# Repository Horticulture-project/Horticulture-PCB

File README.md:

# Horticulture-PCB
Horticulture PCB's

## BOM:
https://htmlpreview.github.io/?https://github.com/Horticulture-project/Horticulture-PCB/blob/master/bom/ibom.html

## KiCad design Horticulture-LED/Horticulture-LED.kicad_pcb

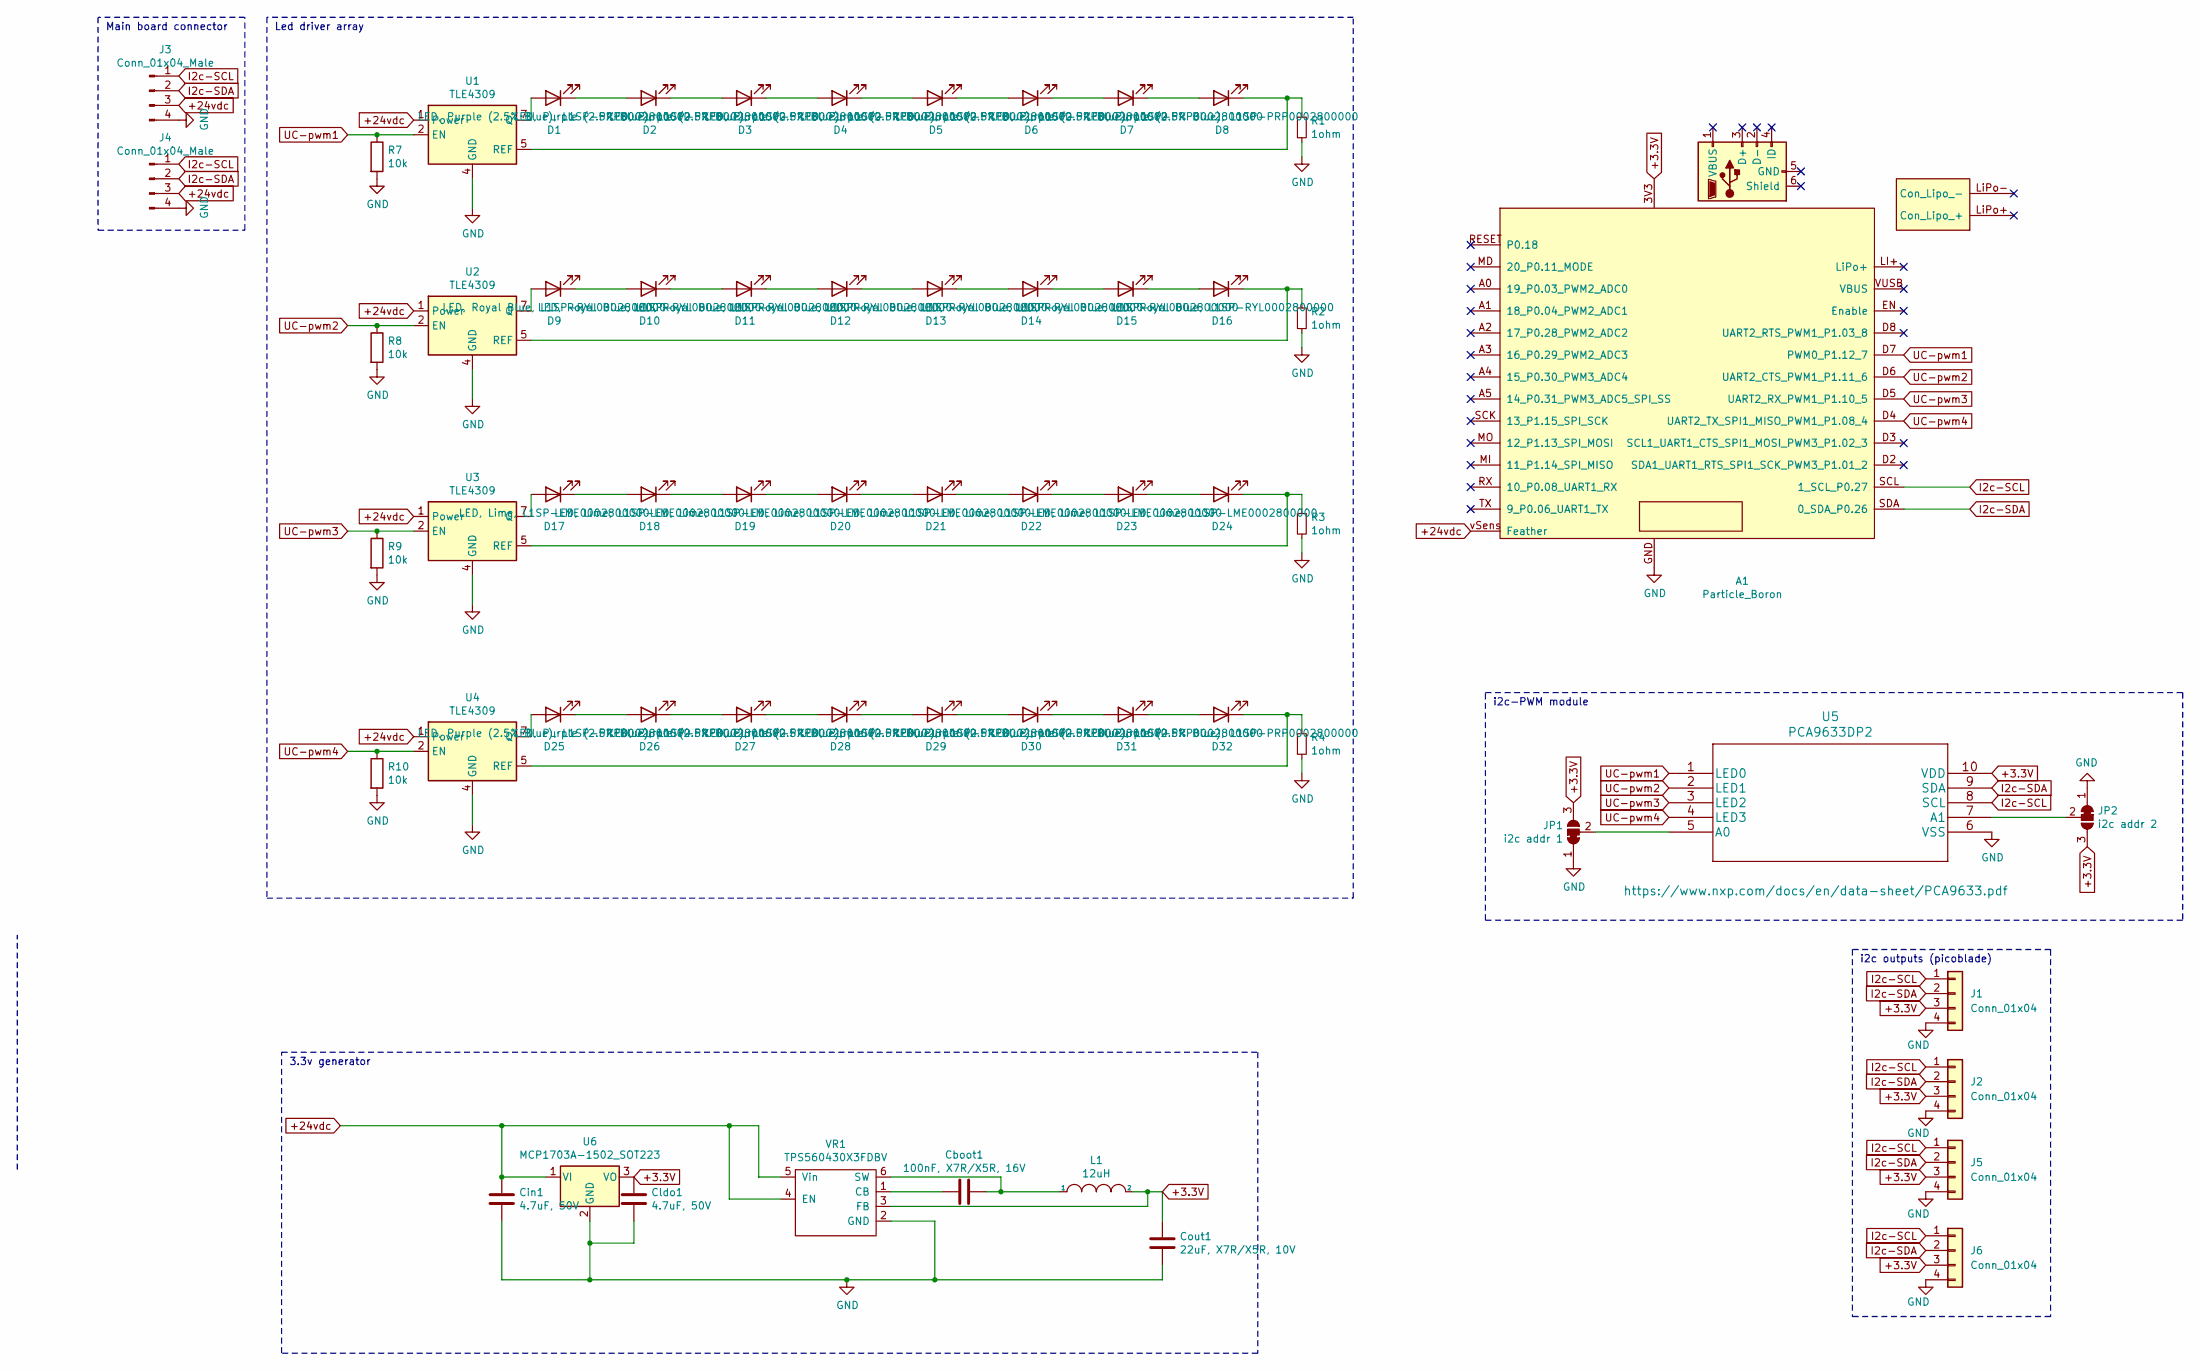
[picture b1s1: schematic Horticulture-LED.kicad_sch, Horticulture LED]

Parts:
A1: Particle_Boron; PCB_FeatherWing
Cboot1: 100nF, X7R/X5R, 16V; C_0805_2012Metric
Cin1: 4.7uF, 50V; C_1206_3216Metric
Cldo1: 4.7uF, 50V; C_1206_3216Metric
Cout1: 22uF, X7R/X5R, 10V; C_0805_2012Metric
D1, D2, D3, D4, D5, D6, D7, D8, D25, D26, D27, D28, D29, D30, D31, D32: LED, Purple (2.5% Blue), L1SP-PRP0002800000; Sunplus-2835
D9, D10, D11, D12, D13, D14, D15, D16: LED, Royal Blue, L1SP-RYL0002800000; Sunplus-2835
D17, D18, D19, D20, D21, D22, D23, D24: LED, Lime, L1SP-LME0002800000; Sunplus-2835
J1, J2, J5, J6: Conn_01x04; Molex_PicoBlade_53398-0471_1x04-1MP_P1.25mm_Vertical
J3, J4: Conn_01x04_Male; JST_XH_S4B-XH-A-1_1x04_P2.50mm_Horizontal-SMD
JP1: i2c addr 1; SolderJumper-3_P1.3mm_Bridged12_RoundedPad1.0x1.5mm_NumberL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
JP2: i2c addr 2; SolderJumper-3_P1.3mm_Bridged12_RoundedPad1.0x1.5mm_NumberL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
L1: 12uH; IND_SDR0403-120ML
R1, R2, R3, R4: 1ohm; R_0805_2012Metric
R7, R8, R9, R10: 10k; R_0402_1005Metric
U1, U2, U3, U4: TLE4309; TO-263-7_TabPin4
U5: PCA9633DP2; SOT-552-1-nxp
U6: MCP1703A-1502_SOT223; SOT-223-3_TabPin2
VR1: TPS560430X3FDBV; SOT-23-6

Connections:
+3.3V: A1.3V3, Cldo1.1, Cout1.1, J1.3, J2.3, J5.3, J6.3, JP1.3 (B), JP2.3 (B), L1.2, U5.10 (VDD), U6.3 (VO), VR1.3 (FB)
+24vdc: A1.vSens (Feather), Cin1.1, J3.3, J4.3, U1.1 (Power), U2.1 (Power), U3.1 (Power), U4.1 (Power), U6.1 (VI), VR1.4 (EN), VR1.5 (Vin)
GND: A1.GND, Cin1.2, Cldo1.2, Cout1.2, J1.4, J2.4, J3.4, J4.4, J5.4, J6.4, JP1.1 (A), JP2.1 (A), R1.2, R2.2, R3.2, R4.2, R7.2, R8.2, R9.2, R10.2, U1.4 (GND), U2.4 (GND), U3.4 (GND), U4.4 (GND), U5.6 (VSS), U6.2 (GND), VR1.2 (GND)
I2c-SCL: A1.SCL (1_SCL_P0.27), J1.1, J2.1, J3.1, J4.1, J5.1, J6.1, U5.8 (SCL)
I2c-SDA: A1.SDA (0_SDA_P0.26), J1.2, J2.2, J3.2, J4.2, J5.2, J6.2, U5.9 (SDA)
unnamed: Cboot1.1, L1.1, VR1.6 (SW)
unnamed: Cboot1.2, VR1.1 (CB)
unnamed: D1.1 (K), D2.2 (A)
unnamed: D1.2 (A), U1.7 (Q)
unnamed: D2.1 (K), D3.2 (A)
unnamed: D3.1 (K), D4.2 (A)
unnamed: D4.1 (K), D5.2 (A)
unnamed: D5.1 (K), D6.2 (A)
unnamed: D6.1 (K), D7.2 (A)
unnamed: D7.1 (K), D8.2 (A)
unnamed: D8.1 (K), R1.1, U1.5 (REF)
unnamed: D9.2 (A), U2.7 (Q)
unnamed: D10.1 (K), D11.2 (A)
unnamed: D9.1 (K), D10.2 (A)
unnamed: D11.1 (K), D12.2 (A)
unnamed: D12.1 (K), D13.2 (A)
unnamed: D13.1 (K), D14.2 (A)
unnamed: D14.1 (K), D15.2 (A)
unnamed: D15.1 (K), D16.2 (A)
unnamed: D16.1 (K), R2.1, U2.5 (REF)
unnamed: D17.1 (K), D18.2 (A)
unnamed: D17.2 (A), U3.7 (Q)
unnamed: D18.1 (K), D19.2 (A)
unnamed: D19.1 (K), D20.2 (A)
unnamed: D20.1 (K), D21.2 (A)
unnamed: D21.1 (K), D22.2 (A)
unnamed: D22.1 (K), D23.2 (A)
unnamed: D23.1 (K), D24.2 (A)
unnamed: D24.1 (K), R3.1, U3.5 (REF)
unnamed: D25.1 (K), D26.2 (A)
unnamed: D25.2 (A), U4.7 (Q)
unnamed: D26.1 (K), D27.2 (A)
unnamed: D27.1 (K), D28.2 (A)
unnamed: D28.1 (K), D29.2 (A)
unnamed: D29.1 (K), D30.2 (A)
unnamed: D30.1 (K), D31.2 (A)
unnamed: D31.1 (K), D32.2 (A)
unnamed: D32.1 (K), R4.1, U4.5 (REF)
unnamed: JP1.2 (C), U5.5 (A0)
unnamed: JP2.2 (C), U5.7 (A1)
UC-pwm1: A1.D7 (PWM0_P1.12_7), R7.1, U1.2 (EN), U5.1 (LED0)
UC-pwm2: A1.D6 (UART2_CTS_PWM1_P1.11_6), R8.1, U2.2 (EN), U5.2 (LED1)
UC-pwm3: A1.D5 (UART2_RX_PWM1_P1.10_5), R9.1, U3.2 (EN), U5.3 (LED2)
UC-pwm4: A1.D4 (UART2_TX_SPI1_MISO_PWM1_P1.08_4), R10.1, U4.2 (EN), U5.4 (LED3)

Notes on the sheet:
i2c-PWM module
Main board connector
i2c outputs (picoblade)
3.3v generator
Led driver array

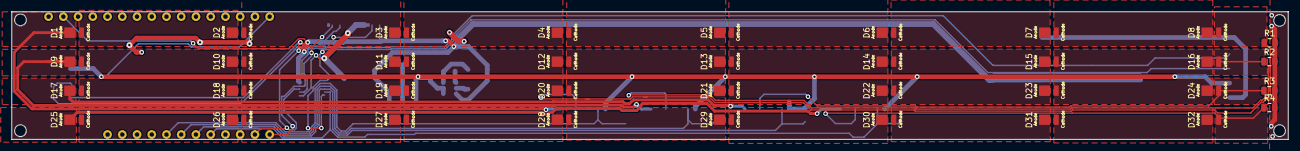
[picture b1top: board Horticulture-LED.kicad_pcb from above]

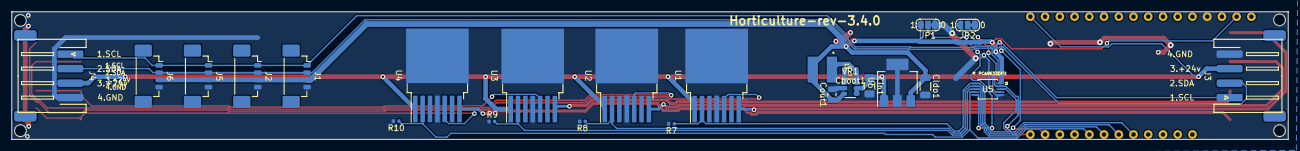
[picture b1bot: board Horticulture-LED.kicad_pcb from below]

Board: 2 copper layers, 219.9 x 22.0 mm, 61 parts (25 on the bottom side), 49 nets.

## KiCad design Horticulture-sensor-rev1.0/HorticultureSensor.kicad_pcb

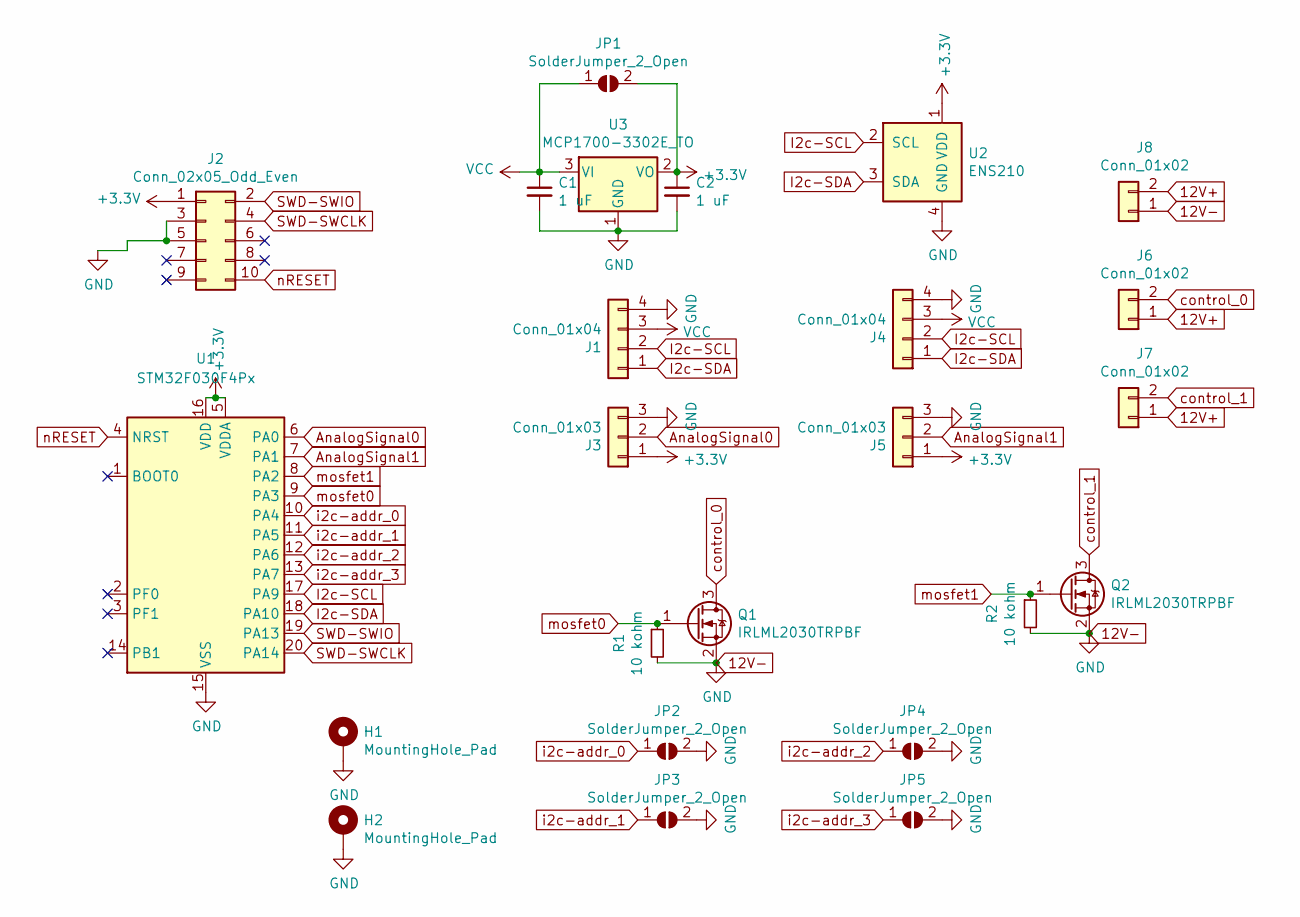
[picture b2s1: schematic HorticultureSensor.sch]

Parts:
C1, C2: 1 uF; C_0805_2012Metric
H1, H2: MountingHole_Pad; MountingHole_3.2mm_M3_Pad
J1, J4: Conn_01x04; JST_XH_S4B-XH-A-1_1x04_P2.50mm_Horizontal
J2: Conn_02x05_Odd_Even; PinHeader_2x05_P1.27mm_Vertical_SMD
J3, J5: Conn_01x03; JST_XH_B3B-XH-A_1x03_P2.50mm_Vertical
J6, J7, J8: Conn_01x02; JST_XH_B2B-XH-AM_1x02_P2.50mm_Vertical
JP1, JP2, JP3, JP4, JP5: SolderJumper_2_Open; SolderJumper-2_P1.3mm_Open_RoundedPad1.0x1.5mm
Q1, Q2: IRLML2030TRPBF; SOT-23
R1, R2: 10 kohm; R_0805_2012Metric
U1: STM32F030F4Px; TSSOP-20_4.4x6.5mm_P0.65mm
U2: ENS210; AMS_QFN-4-1EP_2x2mm_P0.95mm_EP0.7x1.6mm
U3: MCP1700-3302E_TO; SOT-23

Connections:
12V+: J6.1, J7.1, J8.2
12V-: C1.2, C2.2, H1.1, H2.1, J1.4, J2.3, J2.5, J3.3, J4.4, J5.3, J8.1, JP2.2 (B), JP3.2 (B), JP4.2 (B), JP5.2 (B), Q1.2 (S), Q2.2 (S), R1.2, R2.2, U1.15 (VSS), U2.4 (GND), U2.5 (GND), U3.1 (GND)
+3V3: C2.1, J2.1, J3.1, J5.1, JP1.2 (B), U1.5 (VDDA), U1.16 (VDD), U2.1 (VDD), U3.2 (VO)
AnalogSignal0: J3.2, U1.6 (PA0)
AnalogSignal1: J5.2, U1.7 (PA1)
I2c-SCL: J1.2, J4.2, U1.17 (PA9), U2.2 (SCL)
I2c-SDA: J1.1, J4.1, U1.18 (PA10), U2.3 (SDA)
SWD-SWCLK: J2.4, U1.20 (PA14)
SWD-SWIO: J2.2, U1.19 (PA13)
VCC: C1.1, J1.3, J4.3, JP1.1 (A), U3.3 (VI)
control_0: J6.2, Q1.3 (D)
control_1: J7.2, Q2.3 (D)
i2c-addr_0: JP2.1 (A), U1.10 (PA4)
i2c-addr_1: JP3.1 (A), U1.11 (PA5)
i2c-addr_2: JP4.1 (A), U1.12 (PA6)
i2c-addr_3: JP5.1 (A), U1.13 (PA7)
mosfet0: Q1.1 (G), R1.1, U1.9 (PA3)
mosfet1: Q2.1 (G), R2.1, U1.8 (PA2)
nRESET: J2.10, U1.4 (NRST)

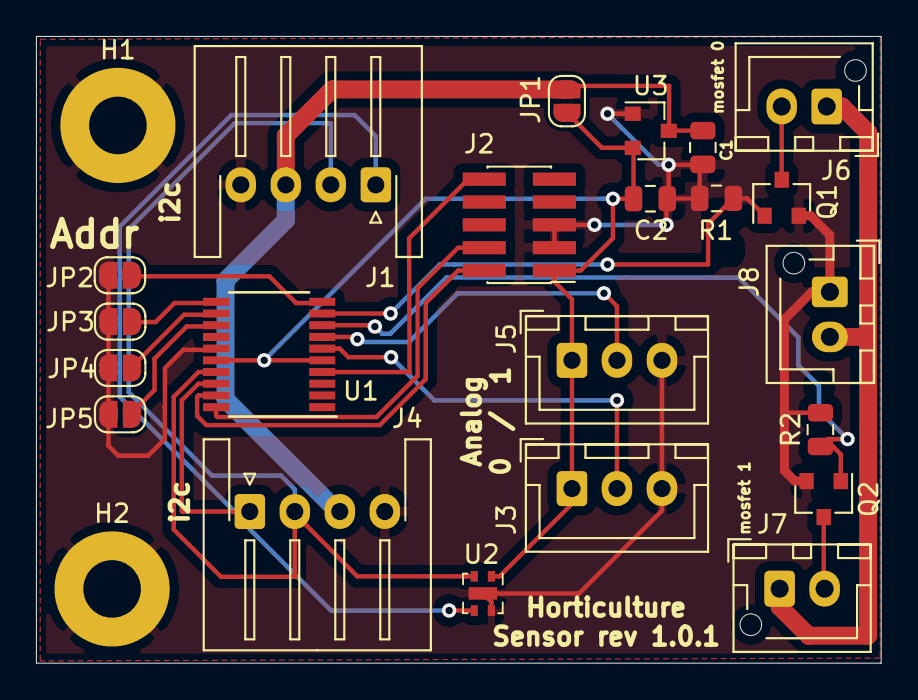
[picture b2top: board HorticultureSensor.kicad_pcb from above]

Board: 2 copper layers, 46.9 x 34.8 mm, 24 parts (0 on the bottom side), 19 nets.

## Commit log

2020-08-10 Initial upload
    Main board rev 3.0.1.0
    Sensor board rev 0.9
2020-08-10 Initial sensor design
    Almost finished, need to work out how power connection should work.
2020-08-13 Working on sensor board
2020-08-13 Sensor board v1 complete
    Not including motor/stepper controller
2020-09-03 Somethings updated
2020-09-09 Joachim: LEDs, particle GND, etc
    Har ikke endret jst connector men har snudd alle leds og fikset på footprints, koblet particle til gnd og fjærnet ferrite bead fordi det trengs ikke aka overkill siden vi ikke har noen veldig sensiti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
2020-10-03 Board file
2020-11-21 Added STM32 testfiles
2020-11-21 added sourcefiles
2020-11-21 update code to remove Led0
2020-11-21 updated clocksource
2020-11-25 Endring av footprints, ny 3.3v løsning, boot0 lagt til gnd, PWM inngang på led-drivers er lagt til gnd med 10k ohm for å hindre forstyrrelser.
2020-11-25 Clean Repo
2020-11-25 Ver 3.2
2020-11-25 Added Gerbers
2020-11-25 Added debounceresistors to Encoder
2020-11-25 Pullup to nRESET
2020-11-25 Added footprint to new resistors
2020-11-30 Added BOM
2020-11-30 Rev-3.2.1
2020-12-01 Fixed dirmarking U1, Resolves #6
2020-12-04 3.2.1 Klar til Produksjon
2020-12-06 3.2.1- RC2. Fixes #4
2020-12-06 3.2.1 RC1 Klar til Produksjon
2020-12-06 rev 3.2.1-final Fixes #2
2020-12-06 Updated schematic info
2021-01-07 Fixed r-values for BOM
2021-01-20 Forbedret LED kjøling med mer kobber på PCB
2021-01-20 Fixed resistor values
2021-01-21 Picoblade connector added for stm programming, minor bug fixes
2021-06-14 Added CI/CD, changed rev in notes to rev in silk layer
    And cleaned repo
2021-06-14 Fixed CD error
2021-06-14 Fixed iBom path error
2021-07-09 Cleaned up, deleted ibom
2021-08-19 More i2c connectors added, fp for 12c/pwm added, removed stm 32 fp, moved tle drivers
2021-08-24 ryddet i resistorer
2021-08-24 fixed GND copper with
2021-08-24 Satt Farge på LED
2021-08-24 Enda mer kobber
2021-08-26 fixes #10 #11 #12
2021-08-26 fixes #11 fixes #12
2021-08-27 Updated rev 3.4.0
2022-02-20 esd-modboard
2022-07-21 Updated to KiCad6
2024-10-08 Updated to kicad 8
2024-11-01 Upgraded kibot action
    Fixed folder name
    Added missing file
2024-11-01 Updated component reference
2024-11-01 Fixed 3.3V i2c references
